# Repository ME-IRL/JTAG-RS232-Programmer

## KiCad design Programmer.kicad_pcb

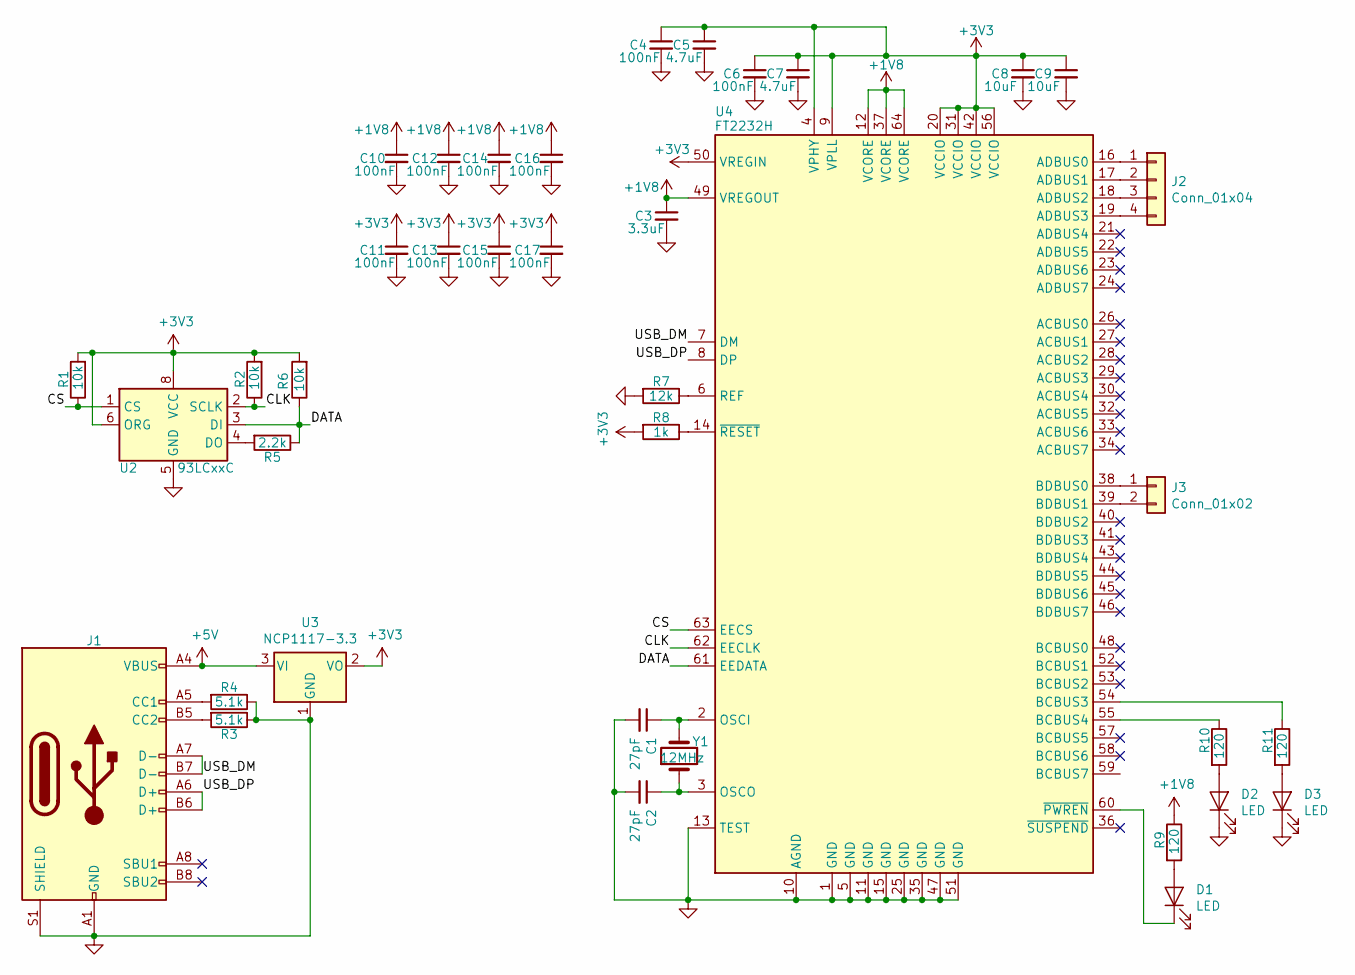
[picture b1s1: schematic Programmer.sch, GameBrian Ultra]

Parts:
C1, C2: 27pF; C_0402_1005Metric
C3: 3.3uF; C_0603_1608Metric
C4, C6, C10, C11, C12, C13, C14, C15, C16, C17: 100nF; C_0402_1005Metric
C5, C7: 4.7uF; C_0402_1005Metric
C8, C9: 10uF; C_0805_2012Metric
D1, D2, D3: LED; D_0805_2012Metric
J1: USB_C_Receptacle_USB2.0; USB_C_Receptacle_Amphenol_12401610E4-2A
J2: Conn_01x04; PinHeader_1x04_P2.54mm_Vertical
J3: Conn_01x02; PinHeader_1x02_P2.54mm_Vertical
R1, R2, R6: 10k; R_0402_1005Metric
R3, R4: 5.1k; R_0805_2012Metric
R5: 2.2k; R_0402_1005Metric
R7: 12k; R_0402_1005Metric
R8: 1k; R_0402_1005Metric
R9, R10, R11: 120; R_0603_1608Metric
U2: 93LCxxC; SOIC-8_3.9x4.9mm_P1.27mm
U3: NCP1117-3.3; SOT-223-3_TabPin2
U4: FT2232H; LQFP-64_10x10mm_P0.5mm
Y1: 12MHz; Crystal_SMD_HC49-SD

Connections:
+1V8: C3.1, C10.1, C12.1, C14.1, C16.1, R9.1, U4.12 (VCORE), U4.37 (VCORE), U4.49 (VREGOUT), U4.64 (VCORE)
+3V3: C4.1, C5.1, C6.1, C7.1, C8.1, C9.1, C11.1, C13.1, C15.1, C17.1, R1.2, R2.2, R6.2, R8.2, U2.6 (ORG), U2.8 (VCC), U3.2 (VO), U4.4 (VPHY), U4.9 (VPLL), U4.20 (VCCIO), U4.31 (VCCIO), U4.42 (VCCIO), U4.50 (VREGIN), U4.56 (VCCIO)
+5V: J1.A4 (VBUS), J1.A9 (VBUS), J1.B4 (VBUS), J1.B9 (VBUS), U3.3 (VI)
/CLK: R2.1, U2.2 (SCLK), U4.62 (EECLK)
/CS: R1.1, U2.1 (CS), U4.63 (EECS)
/DATA: R5.1, R6.1, U2.3 (DI), U4.61 (EEDATA)
/USB_DM: J1.A7 (D-), J1.B7 (D-), U4.7 (DM)
/USB_DP: J1.A6 (D+), J1.B6 (D+), U4.8 (DP)
GND: C1.2, C2.2, C3.2, C4.2, C5.2, C6.2, C7.2, C8.2, C9.2, C10.2, C11.2, C12.2, C13.2, C14.2, C15.2, C16.2, C17.2, D2.1 (K), D3.1 (K), J1.A1 (GND), J1.A12 (GND), J1.B1 (GND), J1.B12 (GND), J1.S1 (SHIELD), R3.1, R4.1, R7.2, U2.5 (GND), U3.1 (GND), U4.1 (GND), U4.5 (GND), U4.10 (AGND), U4.11 (GND), U4.13 (TEST), U4.15 (GND), U4.25 (GND), U4.35 (GND), U4.47 (GND), U4.51 (GND)
unnamed: C1.1, U4.2 (OSCI), Y1.2
unnamed: C2.1, U4.3 (OSCO), Y1.1
unnamed: D1.1 (K), U4.60 (~PWREN)
unnamed: D1.2 (A), R9.2
unnamed: D2.2 (A), R10.2
unnamed: D3.2 (A), R11.2
unnamed: J1.A5 (CC1), R4.2
unnamed: J1.B5 (CC2), R3.2
unnamed: J2.1, U4.16 (ADBUS0)
unnamed: J2.2, U4.17 (ADBUS1)
unnamed: J2.3, U4.18 (ADBUS2)
unnamed: J2.4, U4.19 (ADBUS3)
unnamed: J3.1, U4.38 (BDBUS0)
unnamed: J3.2, U4.39 (BDBUS1)
unnamed: R5.2, U2.4 (DO)
unnamed: R7.1, U4.6 (REF)
unnamed: R8.1, U4.14 (~RESET)
unnamed: R10.1, U4.55 (BCBUS4)
unnamed: R11.1, U4.54 (BCBUS3)

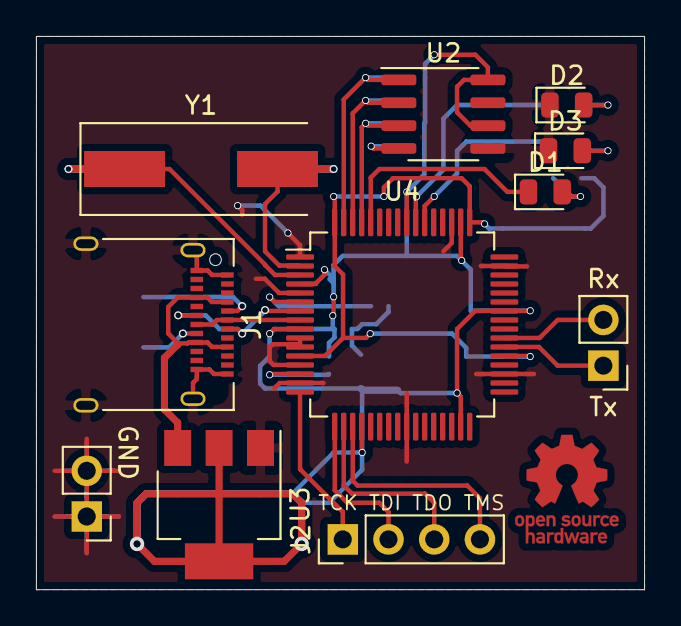
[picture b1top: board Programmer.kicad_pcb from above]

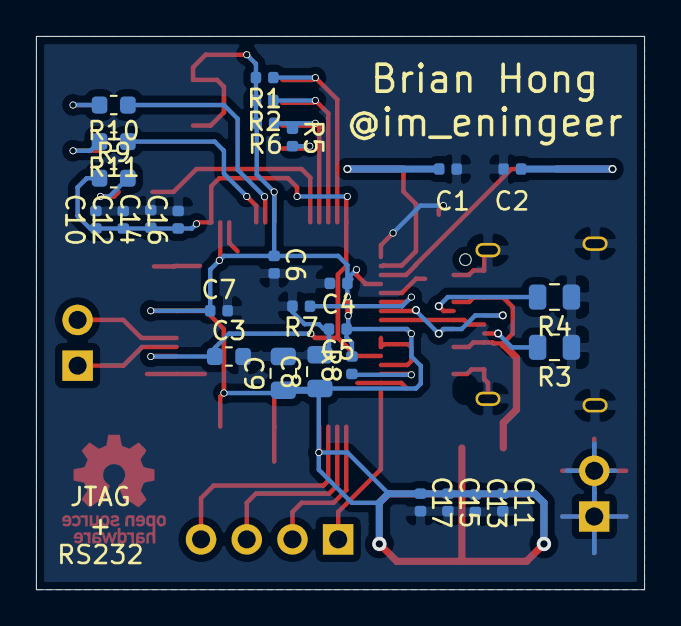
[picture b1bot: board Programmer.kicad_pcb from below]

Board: 2 copper layers, 33.8 x 30.7 mm, 38 parts (28 on the bottom side), 28 nets.

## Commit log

2020-01-10 Revision A
2020-01-11 Revision B
